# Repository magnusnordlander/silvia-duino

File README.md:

# silvia-duino
An Arduino based (simpler) alternative to [magnusnordlander/silvia-pi](https://github.com/magnusnordlander/silvia-pi). The goal is to create a small-footprint PCB that can control a Silvia and do cool things with it, while still being integratable into a smart home.

Project status: Planning

## Components

### PCB
* Arduino Portenta H7
* ADS1220 (for RTDs)
* 78S05 (5V regulator)
* HT7533 (3V3 LDO)
* 2N7002 (for regular SSRs)
* MCP6002 (for amplifying Portenta DAC to 5V)
* SD Card slot (because why not)
* Coin cell battery holder (for RTC, because why not)

### Around the machine
* ETP-RT-4-24-PT100B - SMT Ring Terminal Probe -40 °C 250 °C Pt100, Variohm EuroSensor (boiler sensor)
* ETP-RT-4-24-PT100B - SMT Ring Terminal Probe -40 °C 250 °C Pt100, Variohm EuroSensor (grouphead sensor)
* 128x64 SPI OLED, SSD1309 controller
* Crydom D2425D Dual SSR (Controls heater and solenoid) (Requires >4V for control)
* Pump SSR, either
	* Crydom EZ240D5
	* Crydom MCPC2450A (proportional SSR)
* MIPAF1XX250PSAAX pressure transducer
* Mean-Well APV-8-12 (12V power supply)
* KY-040 Rotary Encoder with switch

## Reference materials

* https://electronics.stackexchange.com/questions/435550/best-practice-on-providing-avdd-and-dvdd-from-single-source
* https://electronics.stackexchange.com/questions/185306/analog-power-ground-planes-doubts/185320#185320

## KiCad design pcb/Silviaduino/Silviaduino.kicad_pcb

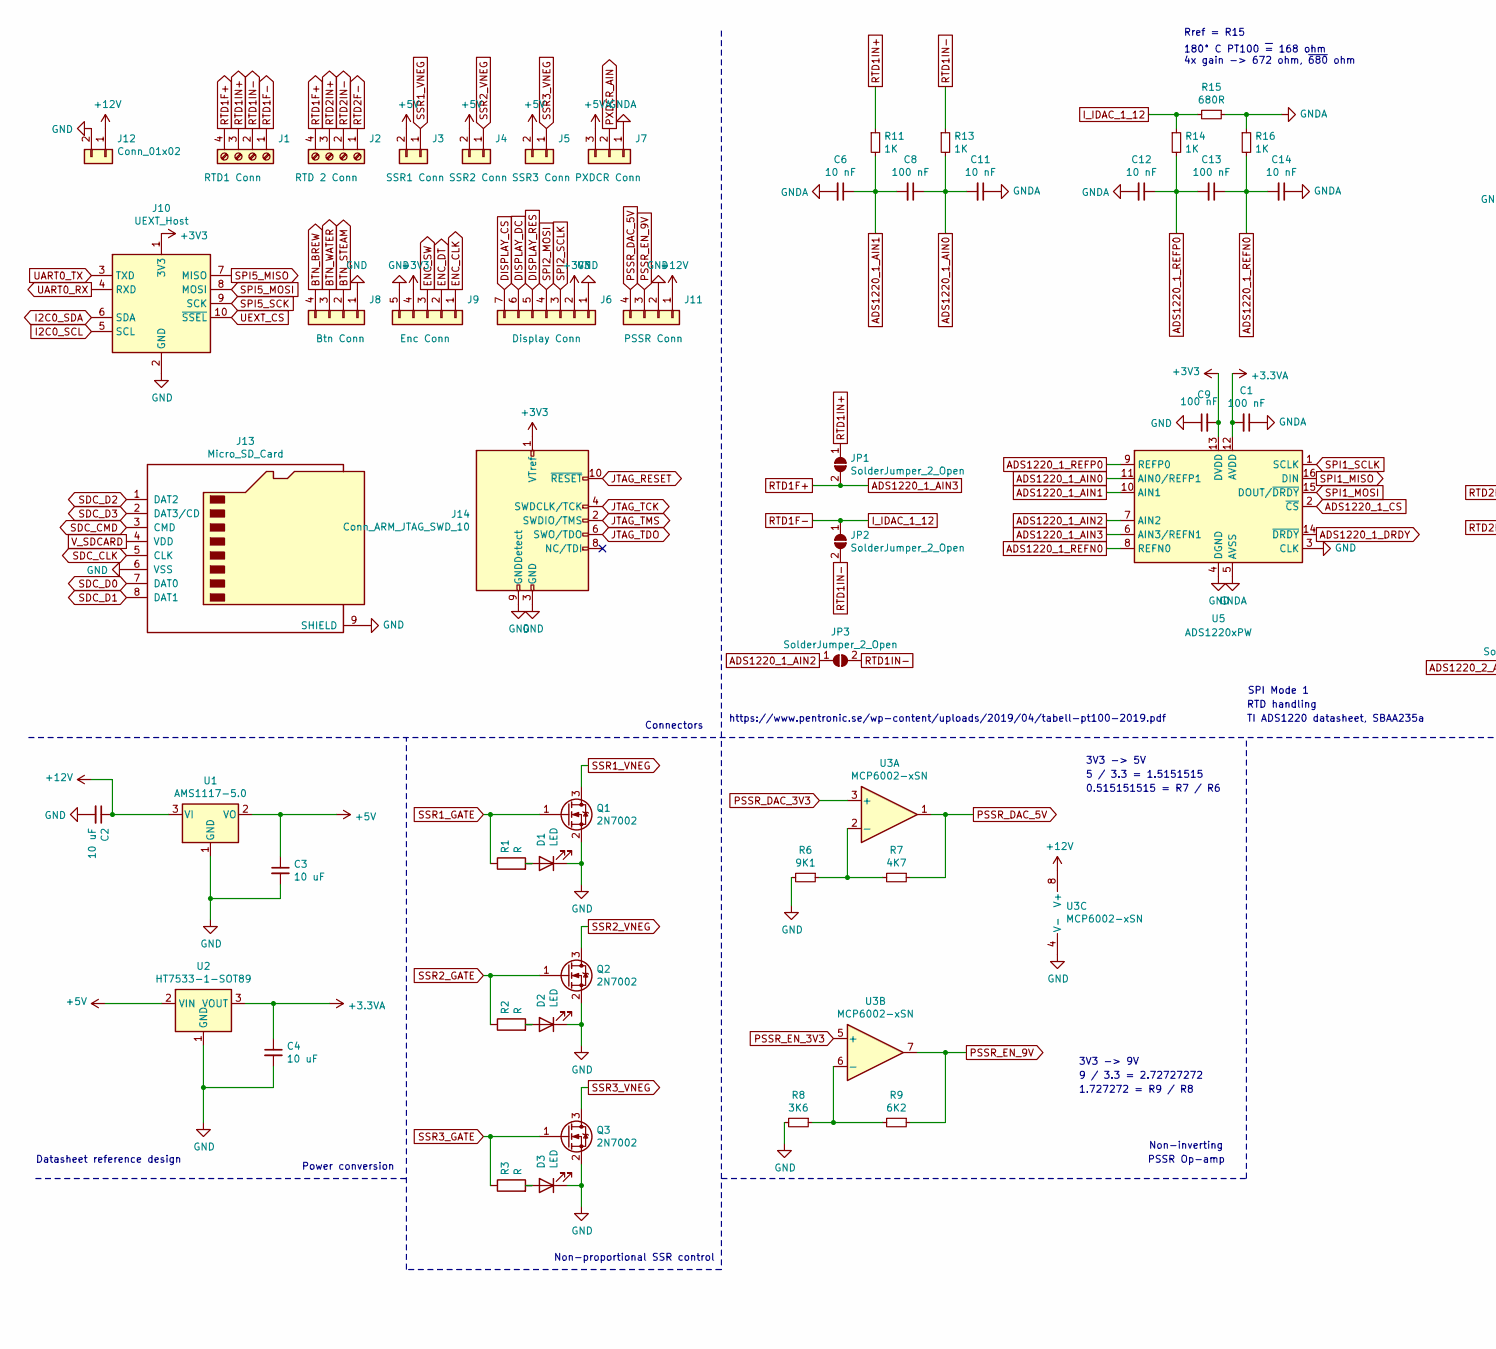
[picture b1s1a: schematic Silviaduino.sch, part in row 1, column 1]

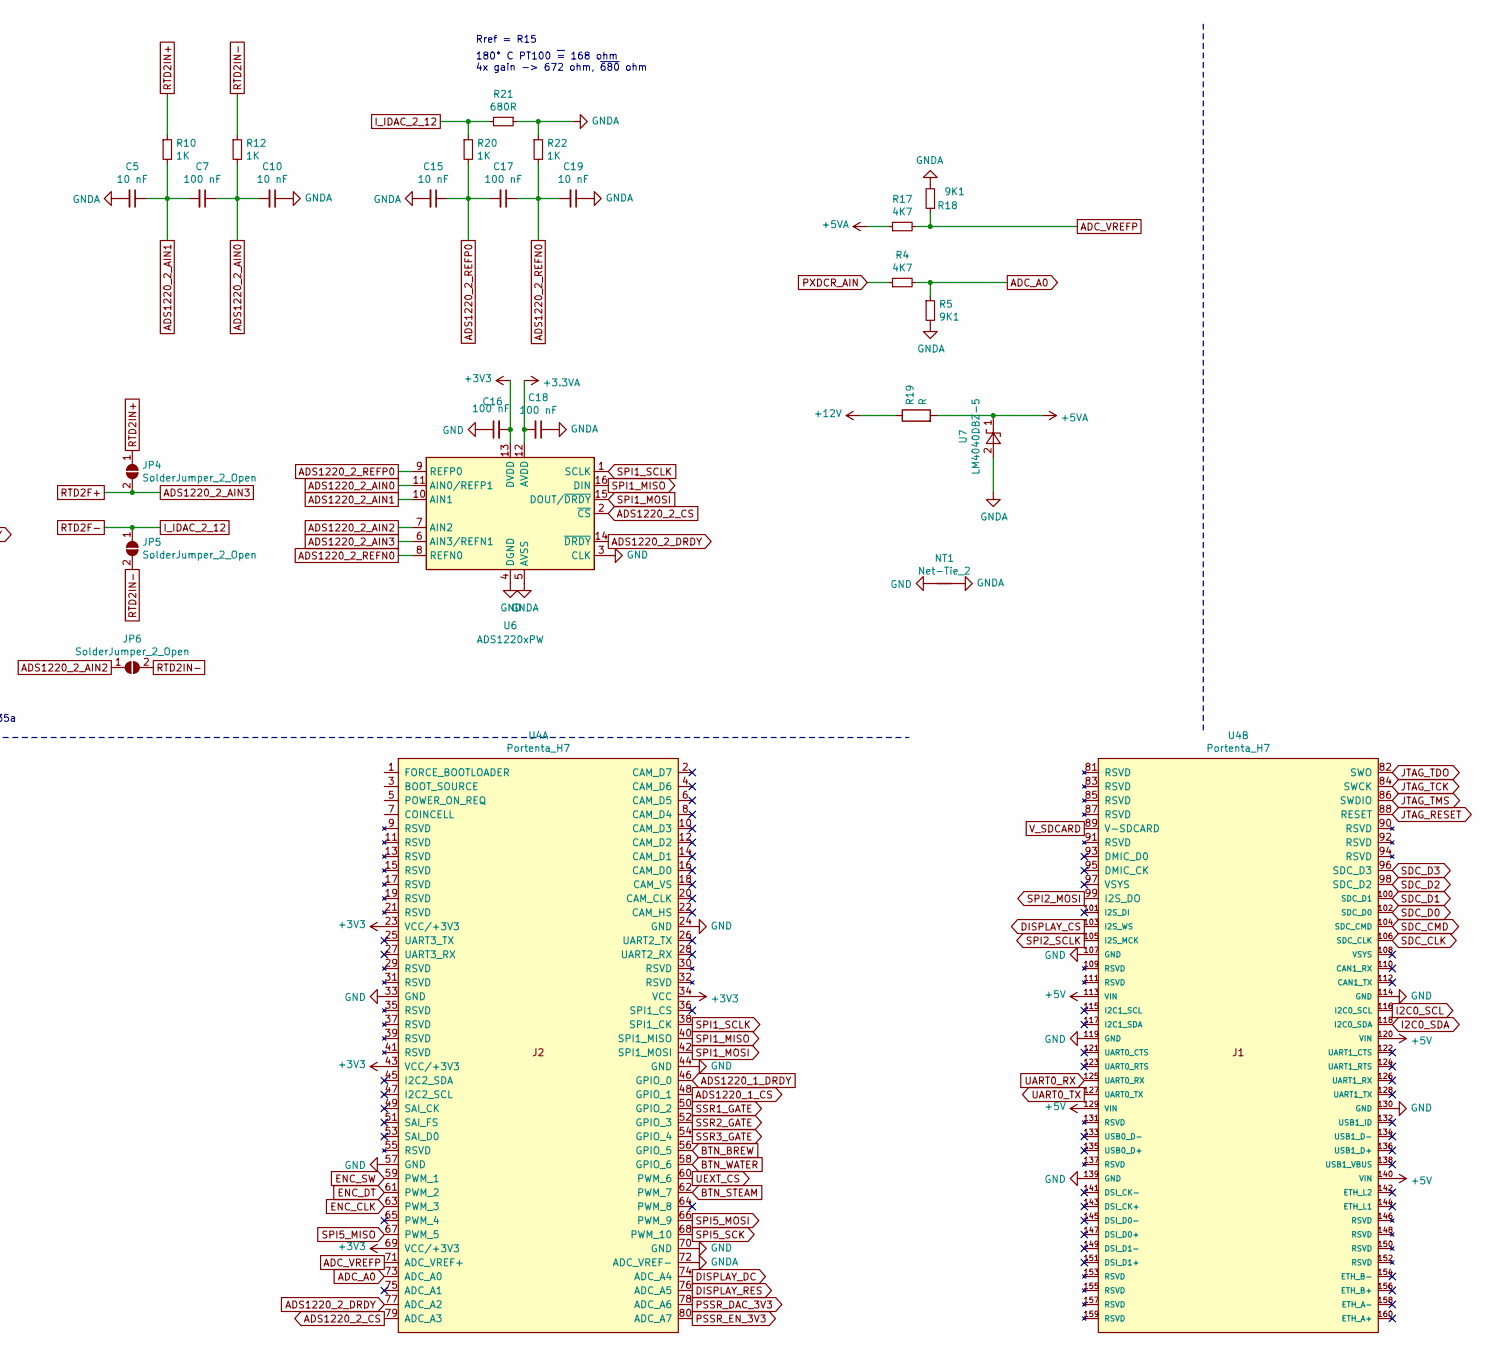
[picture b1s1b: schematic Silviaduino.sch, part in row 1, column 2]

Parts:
C1, C7, C8, C9, C13, C16, C17, C18: 100 nF; C_0402_1005Metric
C2, C3, C4: 10 uF; C_0603_1608Metric
C5, C6, C10, C11, C12, C14, C15, C19: 10 nF; C_0402_1005Metric
D1, D2, D3: LED; LED_0603_1608Metric
J1: RTD1 Conn; PinHeader_1x04_P2.54mm_Vertical
J2: RTD 2 Conn; PinHeader_1x04_P2.54mm_Vertical
J3: SSR1 Conn; PinHeader_1x02_P2.54mm_Vertical
J4: SSR2 Conn; PinHeader_1x02_P2.54mm_Vertical
J5: SSR3 Conn; PinHeader_1x02_P2.54mm_Vertical
J6: Display Conn; PinHeader_1x07_P2.54mm_Vertical
J7: PXDCR Conn; PinHeader_1x03_P2.54mm_Vertical
J8: Btn Conn; PinHeader_1x04_P2.54mm_Vertical
J9: Enc Conn; PinHeader_1x05_P2.54mm_Vertical
J10: UEXT_Host; PinHeader_2x05_P2.54mm_Vertical_SMD
J11: PSSR Conn; PinHeader_1x04_P2.54mm_Vertical
J12: Conn_01x02; PinHeader_1x02_P2.54mm_Vertical
J13: Micro_SD_Card; microSD_HC_Hirose_DM3AT-SF-PEJM5
J14: Conn_ARM_JTAG_SWD_10; PinHeader_2x05_P1.27mm_Vertical_SMD
JP1, JP2, JP3, JP4, JP5, JP6: SolderJumper_2_Open; SolderJumper-2_P1.3mm_Open_RoundedPad1.0x1.5mm
NT1: Net-Tie_2; NetTie-2_SMD_Pad2.0mm
Q1, Q2, Q3: 2N7002; SOT-23
R1, R2, R3: R; R_0402_1005Metric
R4, R7, R17: 4K7; R_0402_1005Metric
R5, R6, R18: 9K1; R_0603_1608Metric
R8: 3K6; R_0603_1608Metric
R9: 6K2; R_0603_1608Metric
R10, R11, R12, R13, R14, R16, R20, R22: 1K; R_0402_1005Metric
R15, R21: 680R; R_Axial_DIN0204_L3.6mm_D1.6mm_P5.08mm_Horizontal
R19: R; R_0603_1608Metric
U1: AMS1117-5.0; SOT-223-3_TabPin2
U2: HT7533-1-SOT89; SOT-89-3
U3: MCP6002-xSN; SOIC-8_3.9x4.9mm_P1.27mm
U4: Portenta_H7; Arduino_Portenta_H7
U5, U6: ADS1220xPW; TSSOP-16_4.4x5mm_P0.65mm
U7: LM4040DBZ-5; SOT-23

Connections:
+3.3VA: C1.2, C4.1, C18.2, U2.3 (VOUT), U5.12 (AVDD), U6.12 (AVDD)
+3V3: C9.2, C16.2, J6.2, J9.4, J10.1 (3V3), J14.1 (VTref), U4.23 (VCC/+3V3), U4.34 (VCC), U4.43 (VCC/+3V3), U4.69 (VCC/+3V3), U5.13 (DVDD), U6.13 (DVDD)
+5V: C3.1, J3.2, J4.2, J5.2, U1.2 (VO), U2.2 (VIN), U4.113 (VIN), U4.120 (VIN), U4.129 (VIN), U4.140 (VIN)
+5VA: J7.3, R17.1, R19.2, U7.1 (K)
+12V: C2.1, J11.1, J12.1, R19.1, U1.3 (VI), U3.8 (V+)
ADC_A0: R4.2, R5.1, U4.73 (ADC_A0)
ADC_VREFP: R17.2, R18.1, U4.71 (ADC_VREF+)
ADS1220_1_AIN0: C8.1, C11.2, R13.2, U5.11 (AIN0/REFP1)
ADS1220_1_AIN1: C6.1, C8.2, R11.2, U5.10 (AIN1)
ADS1220_1_AIN2: JP3.1 (A), U5.7 (AIN2)
ADS1220_1_AIN3: J1.4, J2.4, JP1.2 (B), U5.6 (AIN3/REFN1)
ADS1220_1_CS: U4.48 (GPIO_1), U5.2 (~CS)
ADS1220_1_DRDY: U4.46 (GPIO_0), U5.14 (~DRDY)
ADS1220_1_REFN0: C13.1, C14.2, R16.2, U5.8 (REFN0)
ADS1220_1_REFP0: C12.1, C13.2, R14.2, U5.9 (REFP0)
ADS1220_2_AIN0: C7.1, C10.2, R12.2, U6.11 (AIN0/REFP1)
ADS1220_2_AIN1: C5.1, C7.2, R10.2, U6.10 (AIN1)
ADS1220_2_AIN2: JP6.1 (A), U6.7 (AIN2)
ADS1220_2_AIN3: JP4.2 (B), U6.6 (AIN3/REFN1)
ADS1220_2_CS: U4.79 (ADC_A3), U6.2 (~CS)
ADS1220_2_DRDY: U4.77 (ADC_A2), U6.14 (~DRDY)
ADS1220_2_REFN0: C17.1, C19.2, R22.2, U6.8 (REFN0)
ADS1220_2_REFP0: C15.1, C17.2, R20.2, U6.9 (REFP0)
BTN_BREW: J8.4, U4.56 (GPIO_5)
BTN_STEAM: J8.2, U4.62 (PWM_7)
BTN_WATER: J8.3, U4.58 (GPIO_6)
DISPLAY_CS: J6.7, U4.103 (I2S_WS)
DISPLAY_DC: J6.6, U4.74 (ADC_A4)
DISPLAY_RES: J6.5, U4.76 (ADC_A5)
ENC_CLK: J9.1, U4.63 (PWM_3)
ENC_DT: J9.2, U4.61 (PWM_2)
ENC_SW: J9.3, U4.59 (PWM_1)
GND: C2.2, C3.2, C4.2, C9.1, C16.1, D1.1 (K), D2.1 (K), D3.1 (K), J6.1, J8.1, J9.5, J10.2 (GND), J11.2, J12.2, J13.6 (VSS), J13.9 (SHIELD), J14.3 (GND), J14.5 (GND), J14.9 (GNDDetect), NT1.1, Q1.2 (S), Q2.2 (S), Q3.2 (S), R6.2, R8.2, U1.1 (GND), U2.1 (GND), U3.4 (V-), U4.24 (GND), U4.33 (GND), U4.44 (GND), U4.57 (GND), U4.70 (GND), U4.107 (GND), U4.114 (GND), U4.119 (GND), U4.130 (GND), U4.139 (GND), U5.3 (CLK), U5.4 (DGND), U6.3 (CLK), U6.4 (DGND)
GNDA: C1.1, C5.2, C6.2, C10.1, C11.1, C12.2, C14.1, C15.2, C18.1, C19.1, J7.1, NT1.2, R5.2, R15.1, R16.1, R18.2, R21.1, R22.1, U4.72 (ADC_VREF-), U5.5 (AVSS), U6.5 (AVSS), U7.2 (A)
I2C0_SCL: J10.5 (SCL), U4.116 (I2C0_SCL)
I2C0_SDA: J10.6 (SDA), U4.118 (I2C0_SDA)
I_IDAC_1_12: J1.1, JP2.1 (A), R14.1, R15.2
I_IDAC_2_12: J2.1, JP5.1 (A), R20.1, R21.2
JTAG_RESET: J14.10 (~RESET~), U4.88 (RESET)
JTAG_TCK: J14.4 (SWDCLK/TCK), U4.84 (SWCK)
JTAG_TDO: J14.6 (SWO/TDO), U4.82 (SWO)
JTAG_TMS: J14.2 (SWDIO/TMS), U4.86 (SWDIO)
unnamed: D1.2 (A), R1.2
unnamed: D2.2 (A), R2.2
unnamed: D3.2 (A), R3.2
unnamed: R6.1, R7.2, U3.2 (-)
unnamed: R8.1, R9.2, U3.6 (-)
PSSR_DAC_3V3: U3.3 (+), U4.78 (ADC_A6)
PSSR_DAC_5V: J11.4, R7.1, U3.1
PSSR_EN_3V3: U3.5 (+), U4.80 (ADC_A7)
PSSR_EN_9V: J11.3, R9.1, U3.7
PXDCR_AIN: J7.2, R4.1
RTD1IN+: J1.3, JP1.1 (A), R11.1
RTD1IN-: J1.2, JP2.2 (B), JP3.2 (B), R13.1
RTD2IN+: J2.3, JP4.1 (A), R10.1
RTD2IN-: J2.2, JP5.2 (B), JP6.2 (B), R12.1
SDC_CLK: J13.5 (CLK), U4.106 (SDC_CLK)
SDC_CMD: J13.3 (CMD), U4.104 (SDC_CMD)
SDC_D0: J13.7 (DAT0), U4.102 (SDC_D0)
SDC_D1: J13.8 (DAT1), U4.100 (SDC_D1)
SDC_D2: J13.1 (DAT2), U4.98 (SDC_D2)
SDC_D3: J13.2 (DAT3/CD), U4.96 (SDC_D3)
SPI1_MISO: U4.40 (SPI1_MISO), U5.16 (DIN), U6.16 (DIN)
SPI1_MOSI: U4.42 (SPI1_MOSI), U5.15 (DOUT/~DRDY), U6.15 (DOUT/~DRDY)
SPI1_SCLK: U4.38 (SPI1_CK), U5.1 (SCLK), U6.1 (SCLK)
SPI2_MOSI: J6.4, U4.99 (I2S_DO)
SPI2_SCLK: J6.3, U4.105 (I2S_MCK)
SPI5_MISO: J10.7 (MISO), U4.67 (PWM_5)
SPI5_MOSI: J10.8 (MOSI), U4.66 (PWM_9)
SPI5_SCK: J10.9 (SCK), U4.68 (PWM_10)
SSR1_GATE: Q1.1 (G), R1.1, U4.50 (GPIO_2)
SSR1_VNEG: J3.1, Q1.3 (D)
SSR2_GATE: Q2.1 (G), R2.1, U4.52 (GPIO_3)
SSR2_VNEG: J4.1, Q2.3 (D)
SSR3_GATE: Q3.1 (G), R3.1, U4.54 (GPIO_4)
SSR3_VNEG: J5.1, Q3.3 (D)
UART0_RX: J10.4 (RXD), U4.125 (UART0_RX)
UART0_TX: J10.3 (TXD), U4.127 (UART0_TX)
UEXT_CS: J10.10 (~SSEL), U4.60 (PWM_6)
V_SDCARD: J13.4 (VDD), U4.89 (V-SDCARD)

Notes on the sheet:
TI ADS1220 datasheet, SBAA235a
Datasheet reference design
Power conversion
Connectors
RTD handling
Non-proportional SSR control
SPI Mode 1
PSSR Op-amp
3V3 -> 5V
5 / 3.3 = 1.5151515
Non-inverting
0.515151515 = R7 / R6
3V3 -> 9V
9 / 3.3 = 2.72727272
1.727272 = R9 / R8
Rref = R15
180° C PT100 ~= 168 ohm 4x gain -> 672 ohm, ~680 ohm
https://www.pentronic.se/wp-content/uploads/2019/04/tabell-pt100-2019.pdf

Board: 4 copper layers, 75 parts (10 on the bottom side), 80 nets, no tracks yet.

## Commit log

2021-05-02 Just some experimentation
2021-10-10 Skeleton firmware
2021-10-31 PCB work
